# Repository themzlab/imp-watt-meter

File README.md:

### imp-watt-meter
single-phase energy meter for AC power.  Uses electric imp

The core of this design is the energy metering ic, ADE7953.  This ic does all of the measuring duties.

An electric imp module imp002 is connected with SPI to read the various metrics such as average active power, V*A, instantaneous current and so on.

The electric imp device reads data from the ADE7953 and packages a binary message.
The electric imp agent recieves this data and unpacks it creating a JSON message and http posts this
to a webhost account

A PHP script recieves this message and logs to a file.

Using the electric imp agent, it is possible to redirect the data to one of many
data repository services.

There is a web page using javascript, jquery and highcharts that will allow one to look at current data and also take a snapshot of the current and voltage waveform or else take a 5 second time plot of the power.

**Additional documentation here**

[visit this project on tumblr](http://themzlab.tumblr.com/wattmeter)

Here is a screenshot of the web page

Here is one of the build options.  The case is a PM2425 from polycase.

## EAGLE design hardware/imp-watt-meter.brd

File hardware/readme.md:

Hardware files are Cadsoft Eagle 7.4

for pcb files
oshpark.com

for stencils
ohararp.com

The BOM file has (hopefully) everything ordered from Digikey for the board assembly.

It does not include the wire to board connectors (faston) nor the case, cordgrips
and other mechanical hardware.

An Image of the top of the board

An Image of the bottom of the board.

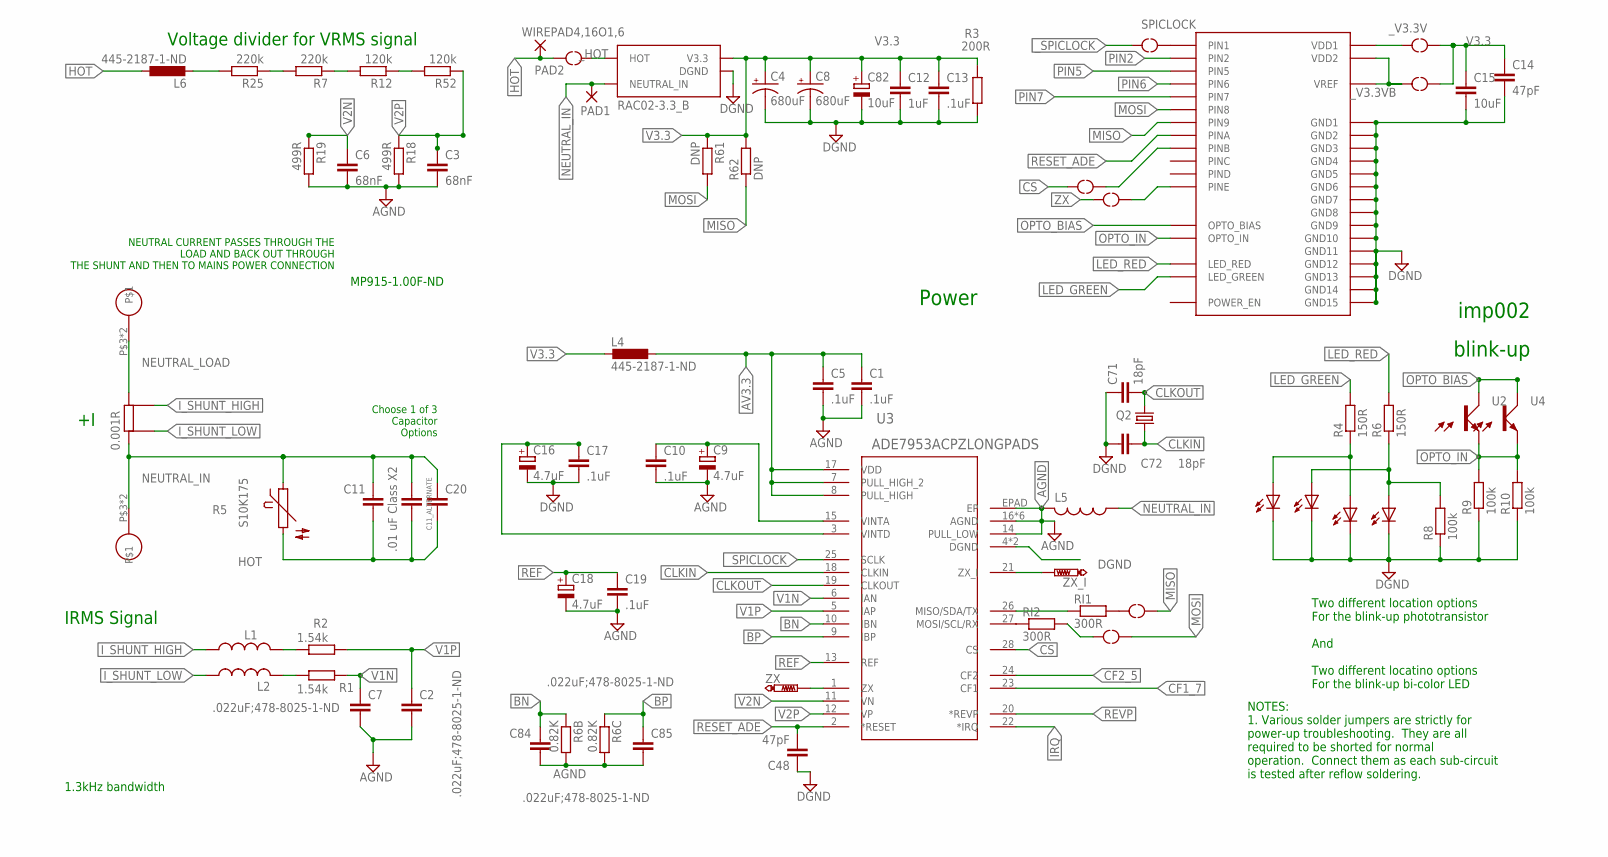
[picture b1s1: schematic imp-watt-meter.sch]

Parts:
0.001R: WSLP2726L5000FEA; WSLP276_VISHAY
C1, C5, C10, C13, C17, C19: .1uF; C0805K@1
C2, C7, C84, C85: .022uF;478-8025-1-ND; C0805K@1
C3, C6: 68nF; C0805K@1
C4, C8: 680uF; PANASONIC_D
C9, C16, C18: 4.7uF; A/3216-18R
C11, C11_ALTERNATE: .01 uF Class X2; C2220K
C12: 1uF; C1206K
C14, C48: 47pF; C0805K@1
C15: 10uF; 1206
C20: C10/4; C10B4
C71, C72: 18pF; C0805K@1
C82: 10uF; A/3216-18R
L1, L2, L5: L-USL4516C; L4516C
L4, L6: 445-2187-1-ND; L2012C
PAD1, PAD2: WIREPAD4,16O1,6; 4,16O1,6
Q2: 535-10200-1-ND; SM49
R1, R2: 1.54k; C0805K
R3: 200R; M1206
R4, R6: 150R; R0805
R5: S10K175
R6B, R6C: 0.82K; C0805K
R7, R25: 220k; R2010
R8, R9, R10: 100k; R0805
R12, R52: 120k; M1206
R18, R19: 499R; C0805K
R61, R62: DNP; C0805K
RI1, RI2: 300R; R0805@1
U1, U5: LED_DUAL; LED-BICOLOR
U2, U4: PHOTOTRANSISTOR0603; 0603
U3: ADE7953ACPZLONGPADS; VQFN-28-D
U$1: RAC02-3.3_B; RAC02_B
U$2, U$17: KEYSTONE_FASTON; KEYSTONE_FASTON_0.25
U$5: IMP002MANUFACTURING; IMP002
U$10, U$11, U$12, U$13, U$15, U$19: JUMPER2B; SOLDER_JUMPER2B
U$16, U$18: JUMPER3; SOLDER_JUMPER3
ZX: PTR1TP08R; TP08R
ZX_I: PTR1TP08R; TP08R

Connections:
AGND: C1.2, C2.2, C3.2, C5.2, C6.2, C7.2, C9.-, C10.2, C18.-, C19.2, C84.2, C85.2, L5.2, R6B.2, R6C.2, R18.2, R19.2, U3.14 (PULL_LOW), U3.16 (AGND), U3.29 (AGND), U3.30 (AGND), U3.31 (AGND), U3.32 (AGND), U3.EPAD (EP), U3._AGND (AGND)
AV3.3: C1.1, C5.1, L4.1, U3.7 (PULL_HIGH_2), U3.8 (PULL_HIGH), U3.17 (VDD)
BN: C84.1, R6B.1, U3.10 (IBN)
BP: C85.1, R6C.1, U3.9 (IBP)
CALIBRATE_HIGH: L6.2, R25.2
CF1_7: U3.23 (CF1)
CF2_5: U3.24 (CF2)
CLKIN: C72.2, Q2.1, U3.18 (CLKIN)
CLKOUT: C71.2, Q2.2, U3.19 (CLKOUT)
CS: U3.28 (CS), U$10.P$2
DGND: C4.-, C8.-, C12.2, C13.2, C14.2, C15.2, C16.-, C17.2, C48.1, C71.1, C72.1, C82.-, R3.2, R8.1, R9.1, R10.1, U1.3 (C), U1.4 (C), U3.4 (DGND), U3._DGND (DGND), U5.3 (C), U5.4 (C), U$1.P$3 (DGND), U$1.P$5 (DGND), U$1.P$8 (DGND), U$1.P$10 (DGND), U$5.PAD1 (GND1), U$5.PAD7 (GND2), U$5.PAD13 (GND3), U$5.PAD17 (GND4), U$5.PAD23 (GND5), U$5.PAD24 (GND6), U$5.PAD25 (GND7), U$5.PAD26 (GND8), U$5.PAD27 (GND9), U$5.PAD28 (GND10), U$5.PAD29 (GND11), U$5.PAD30 (GND12), U$5.PAD31 (GND13), U$5.PAD32 (GND14), U$5.PAD35 (GND15)
HOT: C11.1, C11_ALTERNATE.1, C20.2, L6.1, PAD2.1, R5.2, U$19.P$1
IRQ: U3.22 (*IRQ)
I_SHUNT_HIGH: 0.001R.P$3, L1.1
I_SHUNT_LOW: 0.001R.P$4, L2.1
LED_GREEN: R4.2, U$5.PAD3 (LED_GREEN)
LED_RED: R6.2, U$5.PAD4 (LED_RED)
MISO: R62.1, U$5.PAD14 (PIN9), U$13.P$1
MOSI: R61.2, U$5.PAD22 (PIN8), U$12.P$1
unnamed: L1.2, R2.2
unnamed: R4.1, U1.1 (A), U5.1 (A)
unnamed: R6.1, R8.2, U1.2 (A), U5.2 (A)
NEUTRAL_IN: 0.001R.P$2 (2), 0.001R.P$8 (2), 0.001R.P$9 (2), 0.001R.P$10 (2), C11.2, C11_ALTERNATE.2, C20.1, L5.1, PAD1.1, R5.1, U$1.P$1 (NEUTRAL_IN), U$1.P$6 (NEUTRAL_IN), U$17.P$3, U$17.P$4
NEUTRAL_LOAD: 0.001R.P$1 (1), 0.001R.P$5 (1), 0.001R.P$6 (1), 0.001R.P$7 (1), U$2.P$3, U$2.P$4
OPTO_BIAS: U2.1 (C), U4.1 (C), U$5.PAD2 (OPTO_BIAS)
OPTO_IN: R9.2, R10.2, U2.2 (E), U4.2 (E), U$5.PAD6 (OPTO_IN)
PIN2: U$5.PAD16 (PIN2)
PIN5: U$5.PAD19 (PIN5)
PIN6: U$5.PAD20 (PIN6)
PIN7: U$5.PAD21 (PIN7)
PIN26_MISO_SDA_TX: RI1.1, U3.26 (MISO/SDA/TX)
PIN27_MOSI_SCL_RX: RI2.1, U3.27 (MOSI/SCL/RX)
REF: C18.+, C19.1, U3.13 (REF)
RESET_ADE: C48.2, U3.2 (*RESET), U$5.PAD8 (PINA)
REVP: U3.20 (*REVP)
SDFSDF: L2.2, R1.2
SPICLOCK: U$5.PAD15 (PIN1), U$11.P$1
V1N: C7.1, R1.1, U3.6 (IAN)
V1P: C2.1, R2.1, U3.5 (IAP)
V2N: C6.1, R19.1, U3.11 (VN)
V2P: C3.1, R18.1, R52.1, U3.12 (VP)
V3.3: C4.+, C8.+, C12.1, C13.1, C14.1, C15.1, C82.+, L4.2, R3.1, R61.1, R62.2, U$1.P$4 (V3.3), U$1.P$9 (V3.3), U$16.P$1, U$18.P$1
VINTA_DCPL: C9.+, C10.1, U3.15 (VINTA)
VINTD_DCPL: C16.+, C17.1, U3.3 (VINTD)
ZX: U3.1 (ZX), U$15.P$2, ZX.TP
ZX_I: U3.21 (ZX_I), ZX_I.TP
_31: R12.1, R52.2
_61: R7.1, R12.2
_118: R7.2, R25.1
_CS: U$5.PAD9 (PINB), U$10.P$1
_HOT: U$1.P$2 (HOT), U$1.P$7 (HOT), U$19.P$2
_I2C_CLOCK_1: RI2.2, U$12.P$2
_I2C_DATA_2: RI1.2, U$13.P$2
_PINE: U$5.PAD12 (PINE), U$15.P$1
_SPICLOCK: U3.25 (SCLK), U$11.P$2
_V3.3V: U$5.PAD18 (VDD1), U$16.P$2
_V3.3VB: U$5.PAD33 (VDD2), U$5.PAD34 (VREF), U$18.P$2

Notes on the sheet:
NEUTRAL CURRENT PASSES THROUGH THE LOAD AND BACK OUT THROUGH THE SHUNT AND THEN TO MAINS POWER CONNECTION
1.3kHz bandwidth
MP915-1.00F-ND
Voltage divider for VRMS signal
blink-up
Power
IRMS Signal
Choose 1 of 3 Capacitor Options
Two different location options For the blink-up phototransistor And Two different locatino options For the blink-up bi-color LED
NOTES: 1. Various solder jumpers are strictly for power-up troubleshooting. They are all required to be shorted for normal operation. Connect them as each sub-circuit is tested after reflow soldering.
imp002

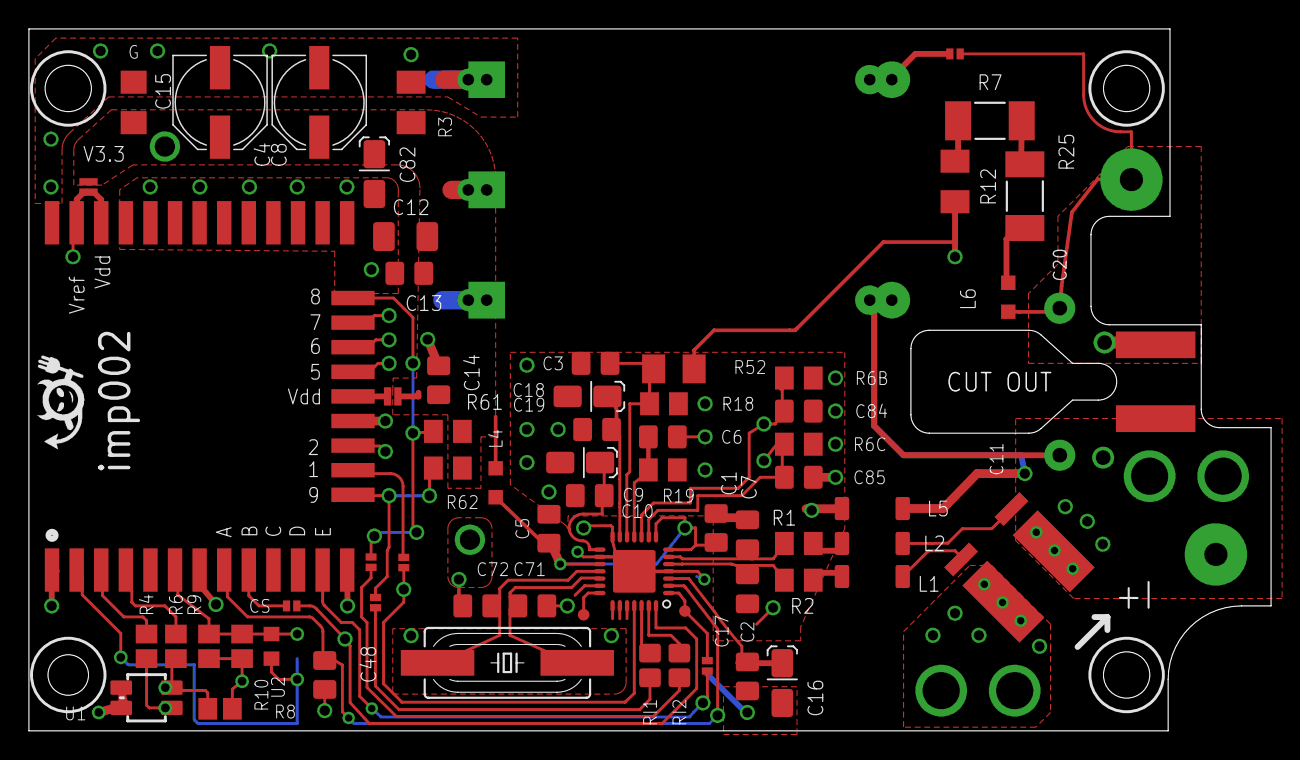
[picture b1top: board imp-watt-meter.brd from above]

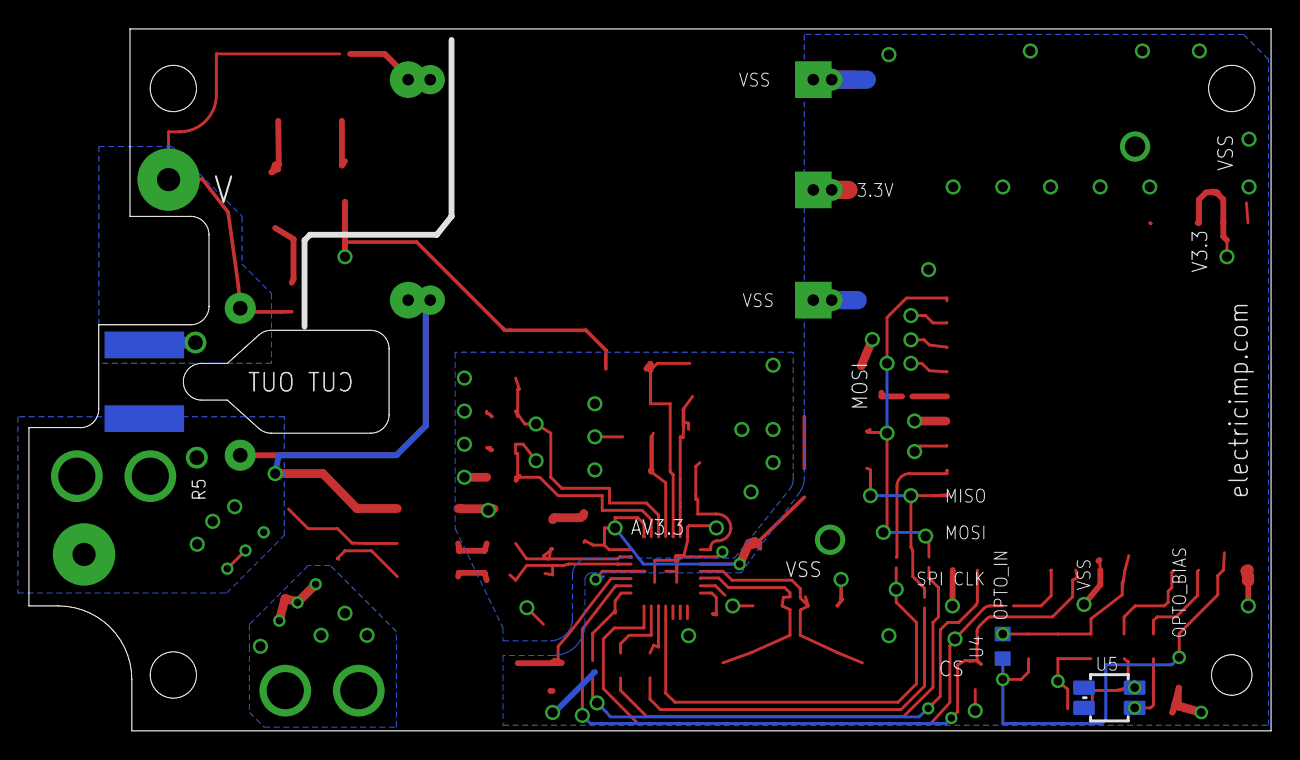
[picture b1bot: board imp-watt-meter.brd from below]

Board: 2 copper layers, 85.9 x 48.5 mm, 76 parts (3 on the bottom side), 49 nets.

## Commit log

2016-01-30 Create watt-meter-agent
2016-01-30 Create watt-meter-device
2016-01-30 Rename electric_imp/log_impeeid.php to electric_implog_impeeid.php
2016-02-02 Create screenshots
2016-02-03 Update watt-meter-agent
2016-02-03 Create test
2016-02-05 Update watt-meter-device
2016-02-05 updated name of nets to reflect that SPI is used, not i2c
2016-02-05 reflect use of SPI, not i2c in name of nets
2016-02-05 test
2016-02-05 another test
2016-02-13 renamed so I could set up default editor using Squirrel's .nut extension
2016-02-13 testing...
2016-02-13 clarified note on schematic
2016-02-13 testing

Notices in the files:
parts and their libraries:
SparkFun-Passives: Licensing: CC v3.0 Share-Alike You are welcome to use this library for commercial purposes.
